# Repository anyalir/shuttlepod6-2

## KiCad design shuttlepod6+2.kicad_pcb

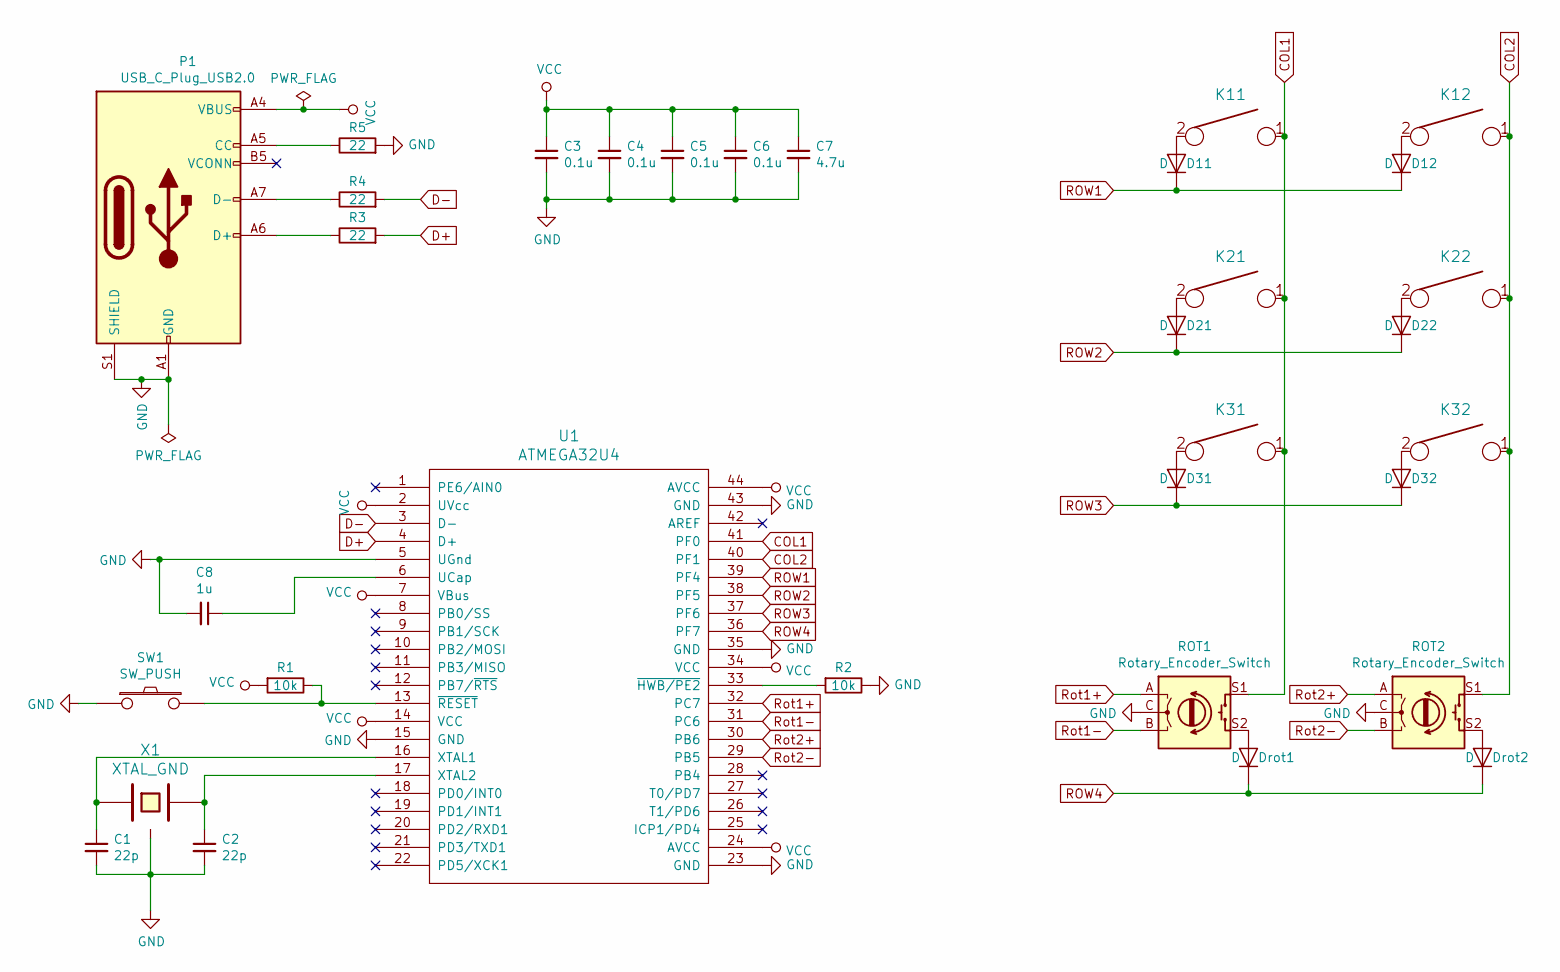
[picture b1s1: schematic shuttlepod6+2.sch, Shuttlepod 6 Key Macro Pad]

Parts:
C1, C2: 22p; C_0805_2012Metric_Pad1.15x1.40mm_HandSolder
C3, C4, C5, C6: 0.1u; C_0805_2012Metric_Pad1.15x1.40mm_HandSolder
C7: 4.7u; C_0805_2012Metric_Pad1.15x1.40mm_HandSolder
C8: 1u; C_0805_2012Metric_Pad1.15x1.40mm_HandSolder
D11, D12, D21, D22, D31, D32: D; D_SOD123_hand
Drot1, Drot2: D; D_SOD123_hand
K11, K12, K21, K22, K31, K32: KEYSW; Mx_Alps_100
P1: USB_C_Plug_USB2.0; 12401598E4#2A
R1, R2: 10k; R_0805_2012Metric_Pad1.15x1.40mm_HandSolder
R3, R4, R5: 22; R_0805_2012Metric_Pad1.15x1.40mm_HandSolder
ROT1, ROT2: Rotary_Encoder_Switch; RotaryEncoder_Alps_EC11E-Switch_Vertical_H20mm
SW1: SW_PUSH; SW_SPST_TL3342
U1: ATMEGA32U4; QFP44
X1: XTAL_GND; FA-238

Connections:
COL1: K11.1, K21.1, K31.1, ROT1.S1, U1.41 (PF0)
COL2: K12.1, K22.1, K32.1, ROT2.S1, U1.40 (PF1)
D+: R3.2, U1.4 (D+)
D-: R4.2, U1.3 (D-)
GND: C1.2, C2.2, C3.2, C4.2, C5.2, C6.2, C7.2, C8.2, P1.A1 (GND), P1.A12 (GND), P1.B1 (GND), P1.B12 (GND), P1.S1 (SHIELD), R2.1, R5.2, ROT1.C, ROT2.C, SW1.1, U1.5 (UGnd), U1.15 (GND), U1.23 (GND), U1.35 (GND), U1.43 (GND), X1.3
unnamed: C1.1, U1.16 (XTAL1), X1.1
unnamed: C2.1, U1.17 (XTAL2), X1.2
unnamed: C8.1, U1.6 (UCap)
unnamed: D11.2 (A), K11.2
unnamed: D12.2 (A), K12.2
unnamed: D21.2 (A), K21.2
unnamed: D22.2 (A), K22.2
unnamed: D31.2 (A), K31.2
unnamed: D32.2 (A), K32.2
unnamed: Drot1.2 (A), ROT1.S2
unnamed: Drot2.2 (A), ROT2.S2
unnamed: P1.A5 (CC), R5.1
unnamed: P1.A6 (D+), R3.1
unnamed: P1.A7 (D-), R4.1
unnamed: R1.1, SW1.2, U1.13 (~RESET)
unnamed: R2.2, U1.33 (~HWB/PE2)
ROW1: D11.1 (K), D12.1 (K), U1.39 (PF4)
ROW2: D21.1 (K), D22.1 (K), U1.38 (PF5)
ROW3: D31.1 (K), D32.1 (K), U1.37 (PF6)
ROW4: Drot1.1 (K), Drot2.1 (K), U1.36 (PF7)
Rot1+: ROT1.A, U1.32 (PC7)
Rot1-: ROT1.B, U1.31 (PC6)
Rot2+: ROT2.A, U1.30 (PB6)
Rot2-: ROT2.B, U1.29 (PB5)
VCC: C3.1, C4.1, C5.1, C6.1, C7.1, P1.A4 (VBUS), P1.A9 (VBUS), P1.B4 (VBUS), P1.B9 (VBUS), R1.2, U1.2 (UVcc), U1.7 (VBus), U1.14 (VCC), U1.24 (AVCC), U1.34 (VCC), U1.44 (AVCC)

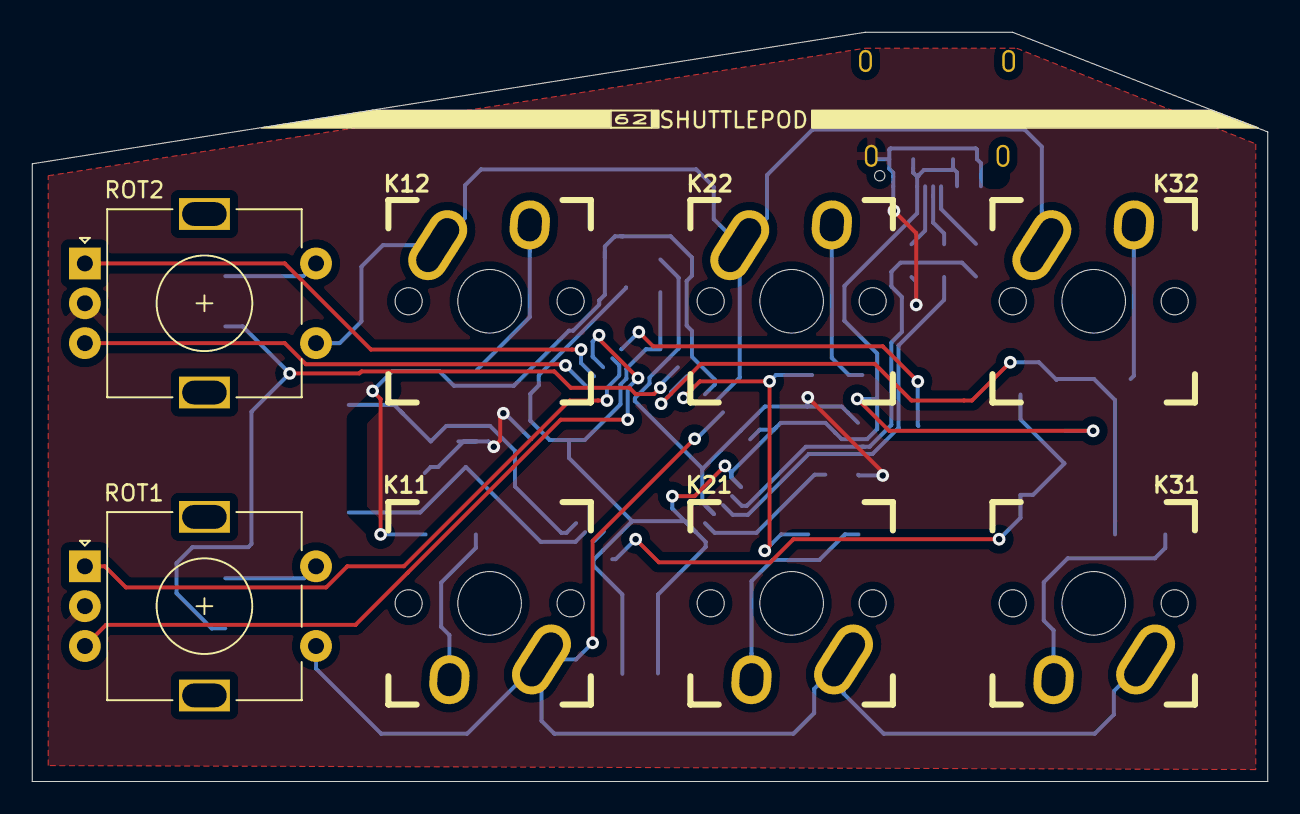
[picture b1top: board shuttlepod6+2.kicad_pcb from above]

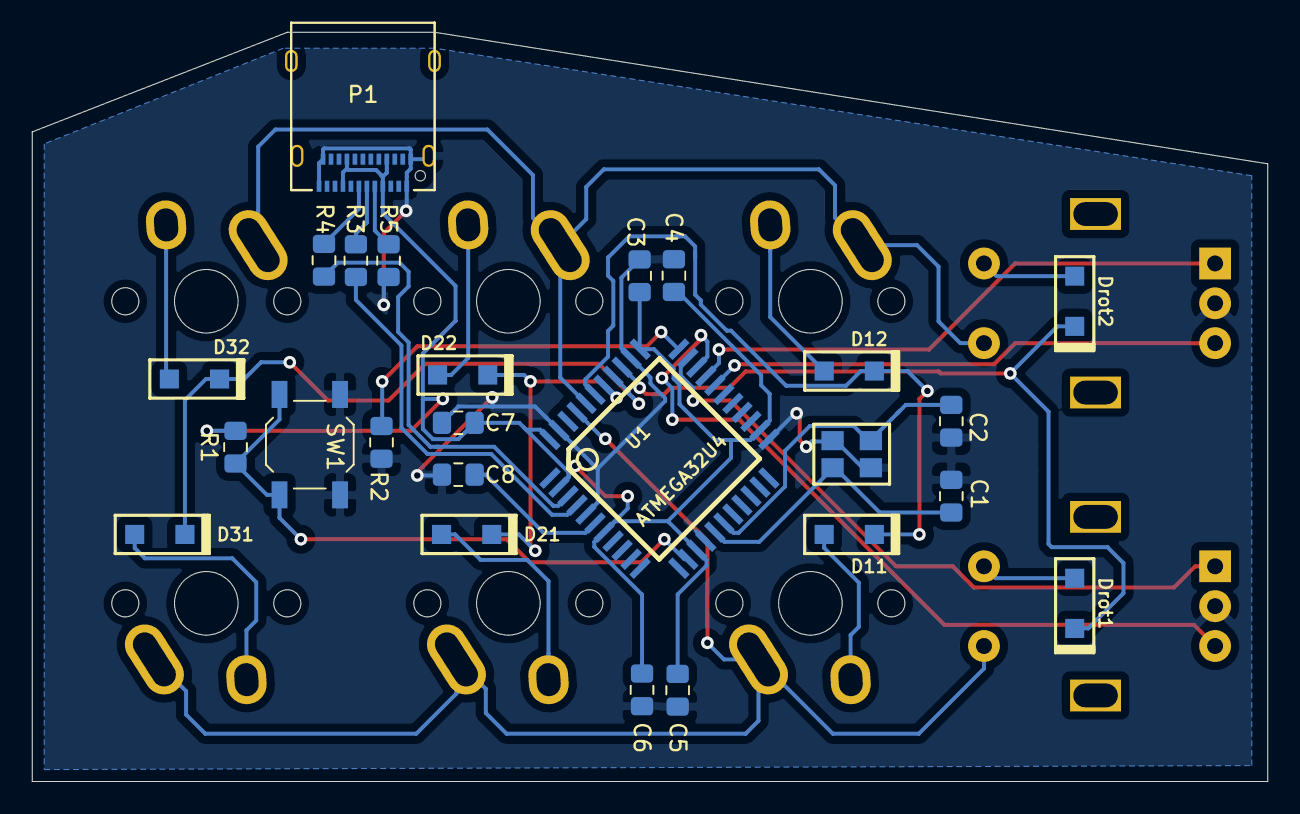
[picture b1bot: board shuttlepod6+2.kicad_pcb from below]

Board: 2 copper layers, 77.5 x 47.0 mm, 33 parts (25 on the bottom side), 30 nets.

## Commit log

2020-04-19 initial: unrouted design with bezel
2020-04-19 changed design, got rid of bezel
2020-04-19 moved crystal closer and better cap placement
2020-04-19 first routing attempt
2020-04-26 even better routing (or so i hope)
